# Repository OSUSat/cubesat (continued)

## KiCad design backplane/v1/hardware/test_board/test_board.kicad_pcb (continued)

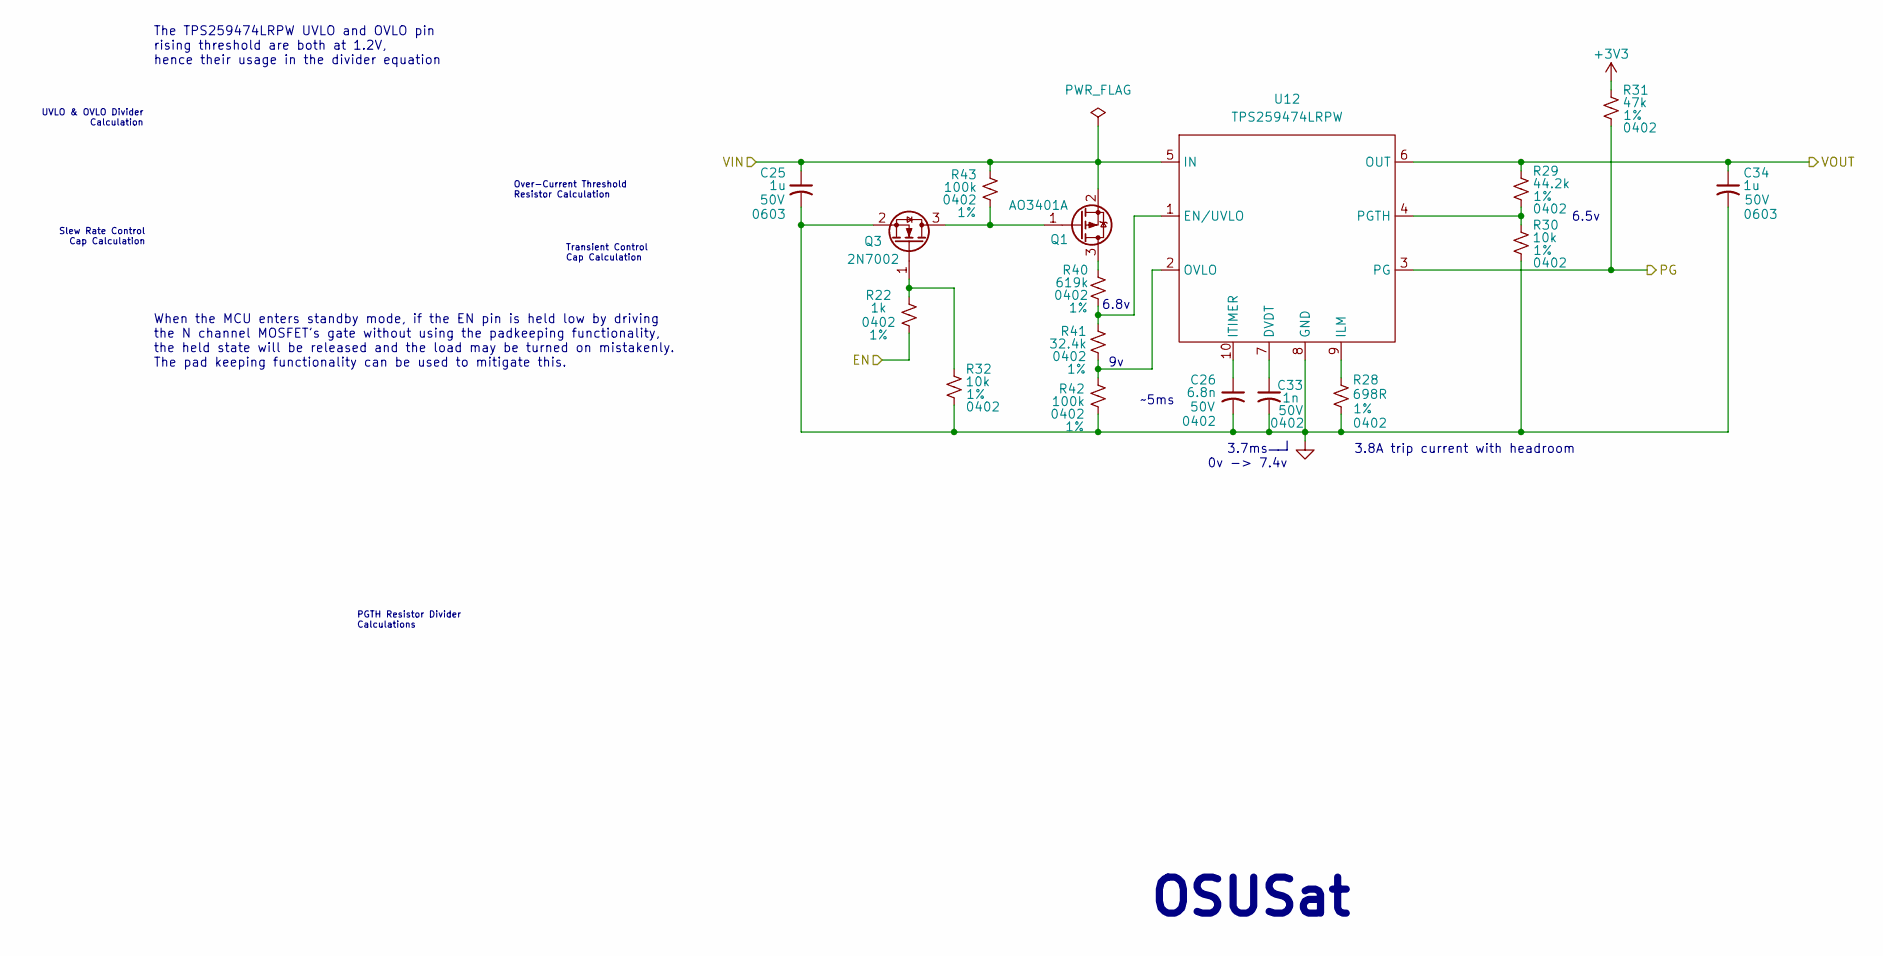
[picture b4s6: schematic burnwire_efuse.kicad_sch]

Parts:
C25, C34: 1u; C_0603_1608Metric; Rating 50V
C26: 6.8n; C_0402_1005Metric; Rating 50V
C33: 1n; C_0402_1005Metric; Rating 50V
Q1: AO3401A; SOT-23
Q3: 2N7002; SOT-23
R22: 1k; R_0402_1005Metric; Tolerance 1%; LCSC PN C21190
R28: 698R; R_0402_1005Metric; Tolerance 1%; LCSC PN C4012675
R29: 44.2k; R_0402_1005Metric; Tolerance 1%; LCSC PN C2933098
R30, R32: 10k; R_0402_1005Metric; Tolerance 1%; LCSC PN C25744
R31: 47k; R_0402_1005Metric; Tolerance 1%; LCSC PN C25792
R40: 619k; R_0402_1005Metric; Tolerance 1%; LCSC PN C247117
R41: 32.4k; R_0402_1005Metric; Tolerance 1%; LCSC PN C2933088
R42, R43: 100k; R_0402_1005Metric; Tolerance 1%; LCSC PN C25741
U12: TPS259474LRPW; TPS2594x; MPN TPS259474LRPW; LCSC C2864845

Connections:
+3V3: R31.1; also elsewhere on the board
/Peripherals/BURNWIRE_EN: R22.1; also elsewhere on the board
/Peripherals/PG: R31.2, U12.3 (PG); also elsewhere on the board
/Peripherals/VOUT: C34.1, R29.1, U12.6 (OUT); also elsewhere on the board
/RAIL_8_VOUT: C25.1, Q1.2 (S), R43.1, U12.5 (IN); also elsewhere on the board
GND: C25.2, C26.2, C33.2, C34.2, Q3.2 (S), R28.2, R30.2, R32.2, R42.2, U12.8 (GND); also elsewhere on the board
unnamed: Q1.3 (D), R40.1
unnamed: Q1.1 (G), Q3.3 (D), R43.2
unnamed: Q3.1 (G), R22.2, R32.1
unnamed: C33.1, U12.7 (DVDT)
unnamed: R40.2, R41.1, U12.1 (EN/UVLO)
unnamed: R28.1, U12.9 (ILM)
unnamed: C26.1, U12.10 (ITIMER)
unnamed: R41.2, R42.1, U12.2 (OVLO)
unnamed: R29.2, R30.1, U12.4 (PGTH)

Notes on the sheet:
~5ms
Over-Current Threshold Resistor Calculation
6.8v
PGTH Resistor Divider Calculations
UVLO & OVLO Divider Calculation
Transient Control Cap Calculation
6.5v
Slew Rate Control Cap Calculation
OSUSat
The TPS259474LRPW UVLO and OVLO pin rising threshold are both at 1.2V, hence their usage in the divider equation
3.8A trip current with headroom
When the MCU enters standby mode, if the EN pin is held low by driving the N channel MOSFET's gate without using the padkeeping functionality, the held state will be released and the load may be turned on mistakenly. The pad keeping functionality can be used to mitigate this.
3.7ms 0v -> 7.4v

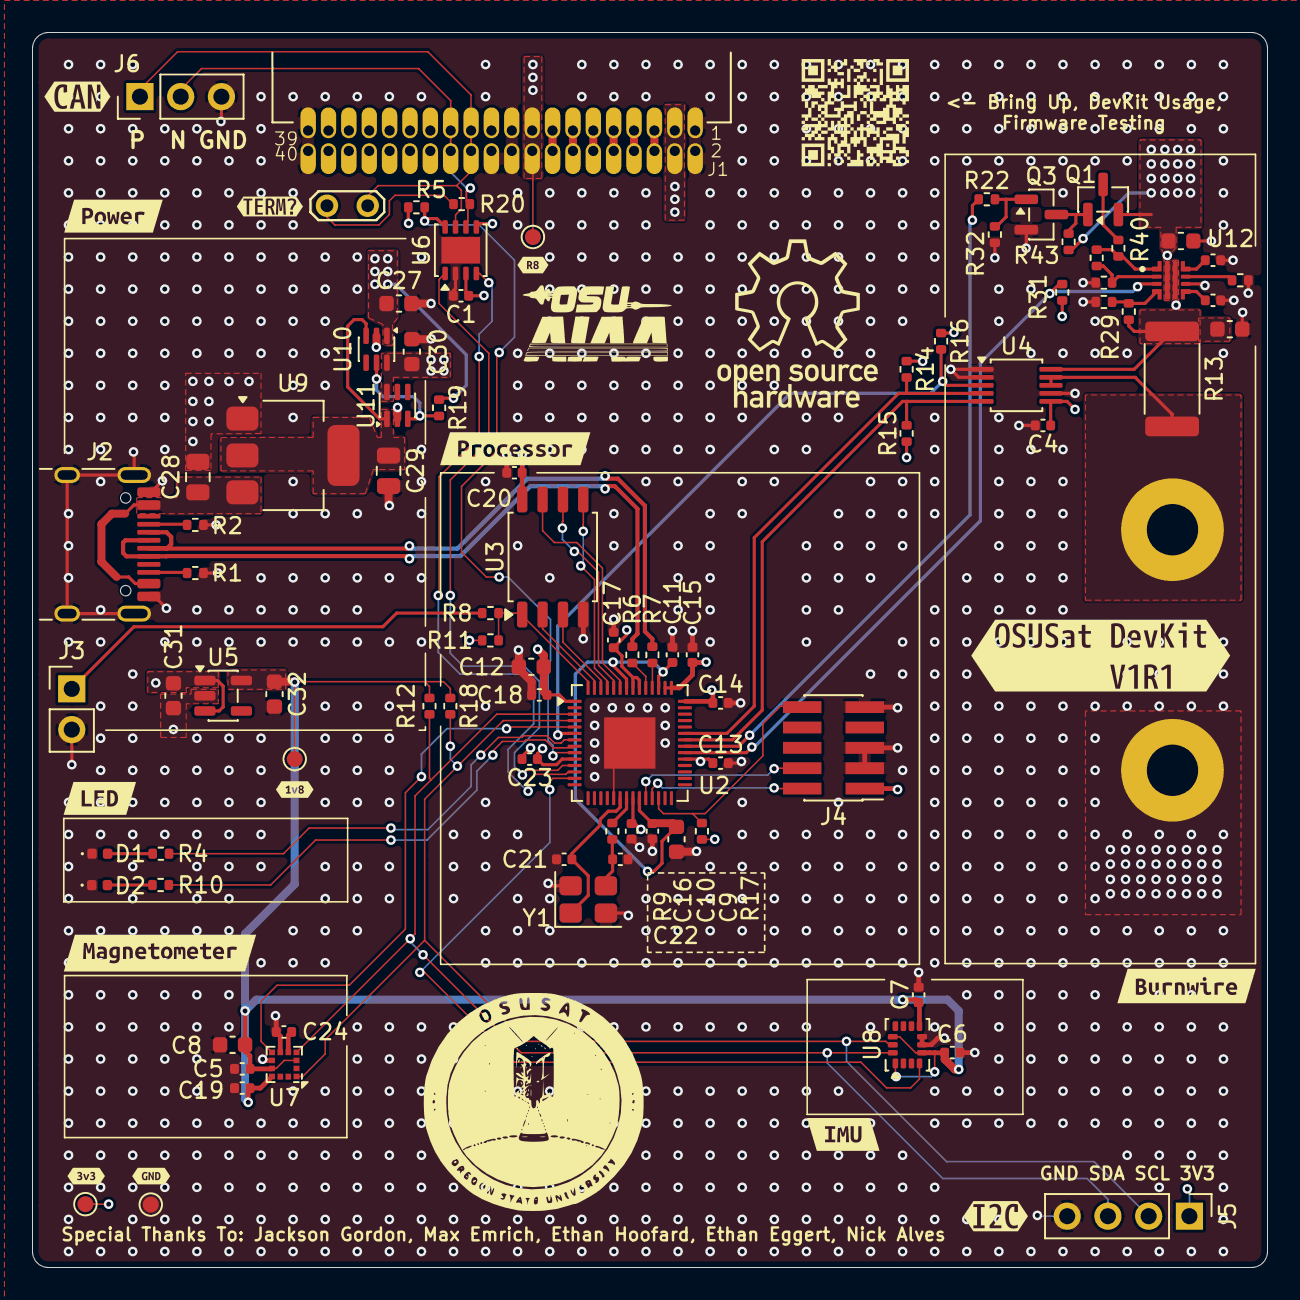
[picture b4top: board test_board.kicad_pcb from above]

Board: 4 copper layers, 77.0 x 77.0 mm, 104 parts (0 on the bottom side), 65 nets.

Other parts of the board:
kibuzzard-6AEEE1A0: G***; kibuzzard-6AEEE1A0
kibuzzard-6AEEE4D9: G***; kibuzzard-6AEEE4D9
kibuzzard-6AEEE4FE: G***; kibuzzard-6AEEE4FE
kibuzzard-6AEEE49C: G***; kibuzzard-6AEEE49C
kibuzzard-6AEEE135: G***; kibuzzard-6AEEE135
kibuzzard-6AEEE141: G***; kibuzzard-6AEEE141
kibuzzard-6AEEE463: G***; kibuzzard-6AEEE463
kibuzzard-6AF0FB3F: G***; kibuzzard-6AF0FB3F
kibuzzard-6AF0FB37: G***; kibuzzard-6AF0FB37
kibuzzard-6AF04FEC: G***; kibuzzard-6AF04FEC
kibuzzard-6AF04FF3: G***; kibuzzard-6AF04FF3
kibuzzard-6AF04FFB: G***; kibuzzard-6AF04FFB
kibuzzard-6AF05A60: G***; kibuzzard-6AF05A60
kibuzzard-6AF14B77: G***; kibuzzard-6AF14B77

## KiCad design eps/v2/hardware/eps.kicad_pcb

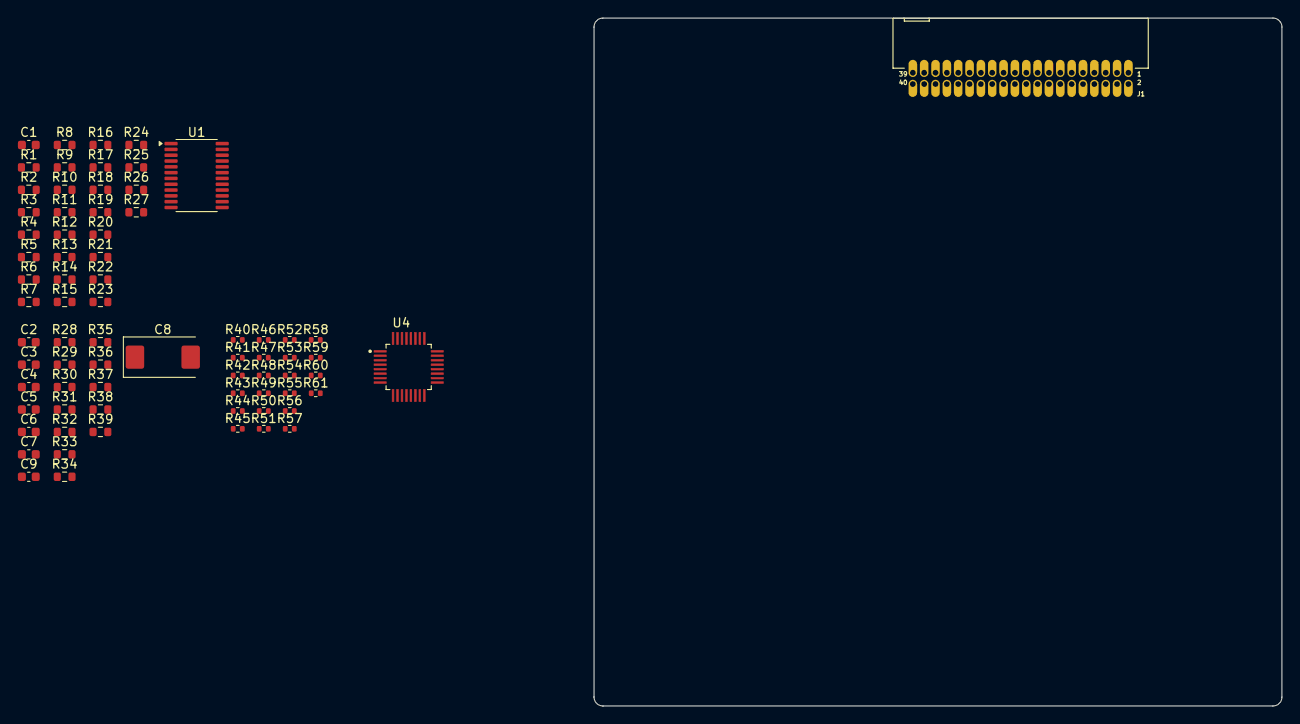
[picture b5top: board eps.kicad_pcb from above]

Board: 2 copper layers, 77.0 x 77.0 mm, 73 parts (0 on the bottom side), 57 nets, no tracks yet.

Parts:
C1: 100n; C_0603_1608Metric
C2, C5: 3.3n 25V; C_0603_1608Metric
C3, C6: 2.2n; C_0603_1608Metric
C4, C7: 1u 25V; C_0603_1608Metric
C8: 220u 25V; CP_EIA-7343-43_Kemet-X
C9: 100n 25V; C_0603_1608Metric
J1: Conn_02x20_Odd_Even; J-SAMTEC-TFM-120-X1-XXX-D-RA
R1, R2, R4, R5, R6, R7, R8, R9, R10, R11, R12, R13, R14, R15, R16, R17, R18, R19: 4.7k; R_0603_1608Metric
R3, R37, R39: 10k; R_0603_1608Metric
R20, R21, R22, R23, R24, R25, R26, R27, R33: 100k; R_0603_1608Metric
R28: 383k; R_0603_1608Metric
R29, R31: 147k; R_0603_1608Metric
R30: 590k; R_0603_1608Metric
R32: 412k; R_0603_1608Metric
R34, R35: 1.13k; R_0603_1608Metric
R36, R38: 220k; R_0603_1608Metric
R40, R41, R42, R43, R44, R45, R46: 47; R_0402_1005Metric
R47, R48, R49, R50, R51, R52, R53, R54, R55, R56, R57, R58: TBD; R_0402_1005Metric
R59, R60, R61: 4.7k; R_0402_1005Metric
U1: TCA9548APWR; TSSOP-24_4.4x7.8mm_P0.65mm
U4: ADS124S08; QFP50P700X700X120-32N

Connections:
+3.3V: U4.15 (IOVDD), U4.16 (DVDD)
+3V3: C1.1, R1.1, R2.1, R3.1, R4.1, R5.1, R6.1, R7.1, R8.1, R9.1, R10.1, R11.1, R12.1, R13.1, R14.1, R15.1, R16.1, R17.1, R18.1, R19.1, R20.1, R36.1, R37.1, R38.1, R39.1, R59.1, R60.1, U1.24 (VCC)
/EPS-ADC-Mux/AIN0: R47.1, R47.2, U4.7 (AIN0)
/EPS-ADC-Mux/AIN1: R48.1, R48.2, U4.6 (AIN1)
/EPS-ADC-Mux/AIN2: R50.1, R50.2, U4.5 (AIN2)
/EPS-ADC-Mux/AIN3: R49.1, R49.2, U4.4 (AIN3)
/EPS-ADC-Mux/AIN4: R51.1, R51.2, U4.3 (AIN4)
/EPS-ADC-Mux/AIN5: R52.1, R52.2, U4.2 (AIN5)
/EPS-ADC-Mux/AIN6: R53.1, R53.2, U4.32 (REFP1/AIN6)
/EPS-ADC-Mux/AIN7: R54.1, R54.2, U4.31 (REFN1/AIN7)
/EPS-ADC-Mux/AIN8: R55.1, R55.2, U4.22 (GPIO0/AIN8)
/EPS-ADC-Mux/AIN9: R56.1, R56.2, U4.21 (GPIO1/AIN9)
/EPS-ADC-Mux/AIN10: R57.1, R57.2, U4.20 (GPIO2/AIN10)
/EPS-ADC-Mux/AIN11: R58.1, R58.2, U4.19 (GPIO3/AIN11)
/EPS-ADC-Mux/CS: R45.2, R60.2, U4.9 (~CS)
/EPS-ADC-Mux/DIN: R44.1, U4.10 (DIN)
/EPS-ADC-Mux/DRDY: R41.1, U4.13 (~DRDY)
/EPS-ADC-Mux/MISO: R42.1, R42.2, U4.12 (DOUT/~DRDY)
/EPS-ADC-Mux/RESET: R40.2, R59.2, U4.18 (~RESET)
/EPS-ADC-Mux/SCLK: R43.1, R43.2, U4.11 (SCLK)
/EPS-ADC-Mux/START/SYNC: R46.1, R46.2, R61.1, U4.8 (START/SYNC)
/Pack-USB-C-Mux/BAT_UVLO: R32.2, R33.1
/Pack-USB-C-Mux/USB_OVLO: R30.2, R31.1
/Pack-USB-C-Mux/USB_UVLO: R28.2, R29.1
CAN_MAIN_N: J1.25, J1.26
CAN_MAIN_P: J1.23, J1.24
EFUSE_I2C_SCL: R1.2, U1.22 (SCL)
EFUSE_I2C_SDA: R2.2, U1.23 (SDA)
EFUSE_R1_SCL: R4.2, U1.5 (SC0)
EFUSE_R1_SDA: R5.2, U1.4 (SD0)
EFUSE_R2_SCL: R6.2, U1.7 (SC1)
EFUSE_R2_SDA: R7.2, U1.6 (SD1)
EFUSE_R3_SCL: R8.2, U1.9 (SC2)
EFUSE_R3_SDA: R9.2, U1.8 (SD2)
EFUSE_R4_SCL: R10.2, U1.11 (SC3)
EFUSE_R4_SDA: R11.2, U1.10 (SD3)
EFUSE_R5_SCL: R12.2, U1.14 (SC4)
EFUSE_R5_SDA: R13.2, U1.13 (SD4)
EFUSE_R6_SCL: R14.2, U1.16 (SC5)
EFUSE_R6_SDA: R15.2, U1.15 (SD5)
EFUSE_R7_SCL: R16.2, U1.18 (SC6)
EFUSE_R7_SDA: R17.2, U1.17 (SD6)
EFUSE_R8_SCL: R18.2, U1.20 (SC7)
EFUSE_R8_SDA: R19.2, U1.19 (SD7)
GND: C1.2, C2.2, C3.2, C4.2, C5.2, C6.2, C7.2, C8.2, C9.2, J1.1, J1.2, J1.19, J1.20, J1.22, J1.39, J1.40, R21.2, R22.2, R23.2, R24.2, R25.2, R26.2, R27.2, R29.2, R31.2, R33.2, R34.2, R35.2, R61.2, U1.1 (A0), U1.2 (A1), U1.12 (GND), U1.21 (A2), U4.1 (AINCOM), U4.14 (DGND), U4.17 (CLK), U4.24 (REFCOM), U4.27 (AVSS), U4.28 (AVSS-SW)
I2C_MUX_RST: R3.2, U1.3 (~RESET)
PACK_V: C7.1, R32.1
RAIL_1_VOUT: J1.3, J1.4
RAIL_2_VOUT: J1.5, J1.6
RAIL_3_VOUT: J1.7, J1.8
RAIL_4_VOUT: J1.9, J1.10
RAIL_5_VOUT: J1.11, J1.12
RAIL_6_VOUT: J1.13, J1.14
RAIL_7_VOUT: J1.15, J1.16
RAIL_8_VOUT: J1.17, J1.18
UNREG: C8.1, C9.1
VUSB_PROT: C4.1, R28.1, R30.1

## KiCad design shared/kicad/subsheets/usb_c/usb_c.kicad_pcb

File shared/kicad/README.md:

# OSUSat Shared KiCad Assets & Templates

This directory contains shared KiCad symbols, footprints, 3D models, design rules, library tables, and project templates for the **OSUSat CubeSat** hardware ecosystem.

---

## Directory Contents

- **`templates/`**: Project templates for standard board configurations (e.g. `test_board` expansion cards).
- **`symbols/`**: Shared subsystem component symbol libraries (`OSUSAT_EPS`, `OSUSAT_OBC`, `OSUSAT_Payload`, etc.).
- **`footprints/`**: Shared PCB footprint libraries (`OSUSAT_Connectors.pretty`, `OSUSAT_ICs.pretty`, etc.).
- **`3dmodels/`**: 3D STEP/WRL CAD models for components and mechanical alignments.
- **`rules/`**: Pre-defined DRC rules and PCB stackup definitions.

---

## Adding Templates to KiCad via Symlinking

Symlinking links the shared repository template directory directly into your local KiCad environment. Any updates pulled from git will be available in KiCad without copying files manually.

### Linux Instructions

1. Open a terminal and ensure your KiCad template directory exists:
   ```bash
   mkdir -p ~/.local/share/kicad/10.0/template
   ```
   *(Replace `10.0` with your installed KiCad version: `10.0`, `9.0`, `8.0`, etc.)*

2. Create a symbolic link pointing to the repository template:
   ```bash
   ln -sf /path/to/cubesat/repo/shared/kicad/templates/test_board ~/.local/share/kicad/10.0/template/test_board
   ```

---

### Windows Instructions

#### Option 1: PowerShell
Run PowerShell and execute:

```powershell
# ensure user template directory exists
New-Item -ItemType Directory -Force -Path "$env:APPDATA\kicad\10.0\template"

# create directory symbolic link
New-Item -ItemType SymbolicLink -Path "$env:APPDATA\kicad\10.0\template\test_board" -Target "C:\path\to\cubesat\repo\shared\kicad\templates\test_board"
```
*(Replace `10.0` and `C:\path\to\cubesat` with your installed KiCad version and repo path).*

#### Option 2: Command Prompt (`cmd.exe`)
Open Command Prompt (Run as Administrator):

```cmd
mkdir "%APPDATA%\kicad\10.0\template"
mklink /D "%APPDATA%\kicad\10.0\template\test_board" "C:\path\to\cubesat\shared\kicad\templates\test_board"
```

---

### Alternative: Configure Path in KiCad GUI

1. Open KiCad.
2. Navigate to **Preferences → Configure Paths...**
3. Under **Environment Variables**, add `KICAD_USER_TEMPLATE_DIR`:
   - **Name**: `KICAD_USER_TEMPLATE_DIR`
   - **Path**: Absolute path to `.../cubesat/shared/kicad/templates`
4. Click **OK**.

---

## Creating a Board from Template

1. Open KiCad.
2. Select **File → New Project from Template...** (or `Ctrl+N`).
3. Click the **User Templates** tab.
4. Select **OSUSat Backplane Test Board Template**.
5. Choose your destination directory and enter your project name (e.g. `payload_card_v1`).
6. Click **Save**.

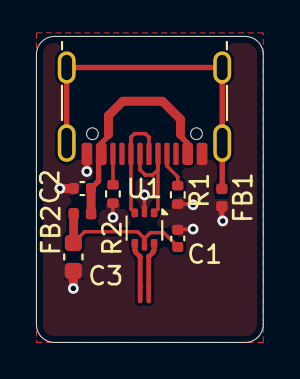
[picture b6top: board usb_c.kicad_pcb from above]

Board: 4 copper layers, 12.6 x 17.0 mm, 9 parts (0 on the bottom side), 8 nets.

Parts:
C1: 100nF; C_0402_1005Metric
C2: 10n; C_0402_1005Metric
C3: 1u; C_0603_1608Metric
FB1, FB2: 120R; L_0402_1005Metric
J1: USB_C_Receptacle_USB2.0_16P; USB_C_Receptacle_G-Switch_GT-USB-7010ASV
R1, R2: 5.1k; R_0402_1005Metric
U1: USBLC6-2P6; SOT-666

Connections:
/USB-C/CC1: J1.A5 (CC1), R1.1
/USB-C/CC2: J1.B5 (CC2), R2.1
/USB-C/FB: FB1.1, J1.SH (SHIELD)
/USB-C/PI: C2.1, FB2.1, J1.A4 (VBUS), J1.A9 (VBUS), J1.B4 (VBUS), J1.B9 (VBUS)
/USB-C/UNPROT_USB_D+: J1.A6 (D+), J1.B6 (D+), U1.3 (I/O2)
/USB-C/UNPROT_USB_D-: J1.A7 (D-), J1.B7 (D-), U1.1 (I/O1)
GND: C1.2, C2.2, C3.2, FB1.2, J1.A1 (GND), J1.A12 (GND), J1.B1 (GND), J1.B12 (GND), R1.2, R2.2, U1.2 (GND)
VBUS: C1.1, C3.1, FB2.2, U1.5 (VBUS)

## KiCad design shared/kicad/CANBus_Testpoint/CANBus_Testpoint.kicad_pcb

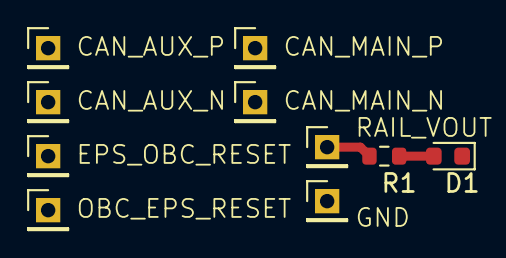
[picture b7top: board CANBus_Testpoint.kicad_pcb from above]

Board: 2 copper layers, 10 parts (0 on the bottom side), 3 nets.

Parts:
CAN_AUX_N_Testpoint1: TP2; PinHeader_1x01_P2.00mm_Vertical
CAN_AUX_P_Testpoint1: TP1; PinHeader_1x01_P2.00mm_Vertical
CAN_MAIN_N_Testpoint1: TP4; PinHeader_1x01_P2.00mm_Vertical
CAN_MAIN_P_Testpoint1: TP3; PinHeader_1x01_P2.00mm_Vertical
D1: LED; LED_0603_1608Metric
EPS_OBC_RESET_Testpoint1: TP5; PinHeader_1x01_P2.00mm_Vertical
GND_Testpoint1: TP8; PinHeader_1x01_P2.00mm_Vertical
OBC_EPS_RESET_Testpoint1: TP6; PinHeader_1x01_P2.00mm_Vertical
R1: R_Small_US; R_0603_1608Metric
RAIL_VOUT_Testpoint1: TP7; PinHeader_1x01_P2.00mm_Vertical

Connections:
/test/RAIL_VOUT: R1.1, RAIL_VOUT_Testpoint1.1 (1_1)
GND: D1.1 (K), GND_Testpoint1.1 (1_1)
unnamed: D1.2 (A), R1.2

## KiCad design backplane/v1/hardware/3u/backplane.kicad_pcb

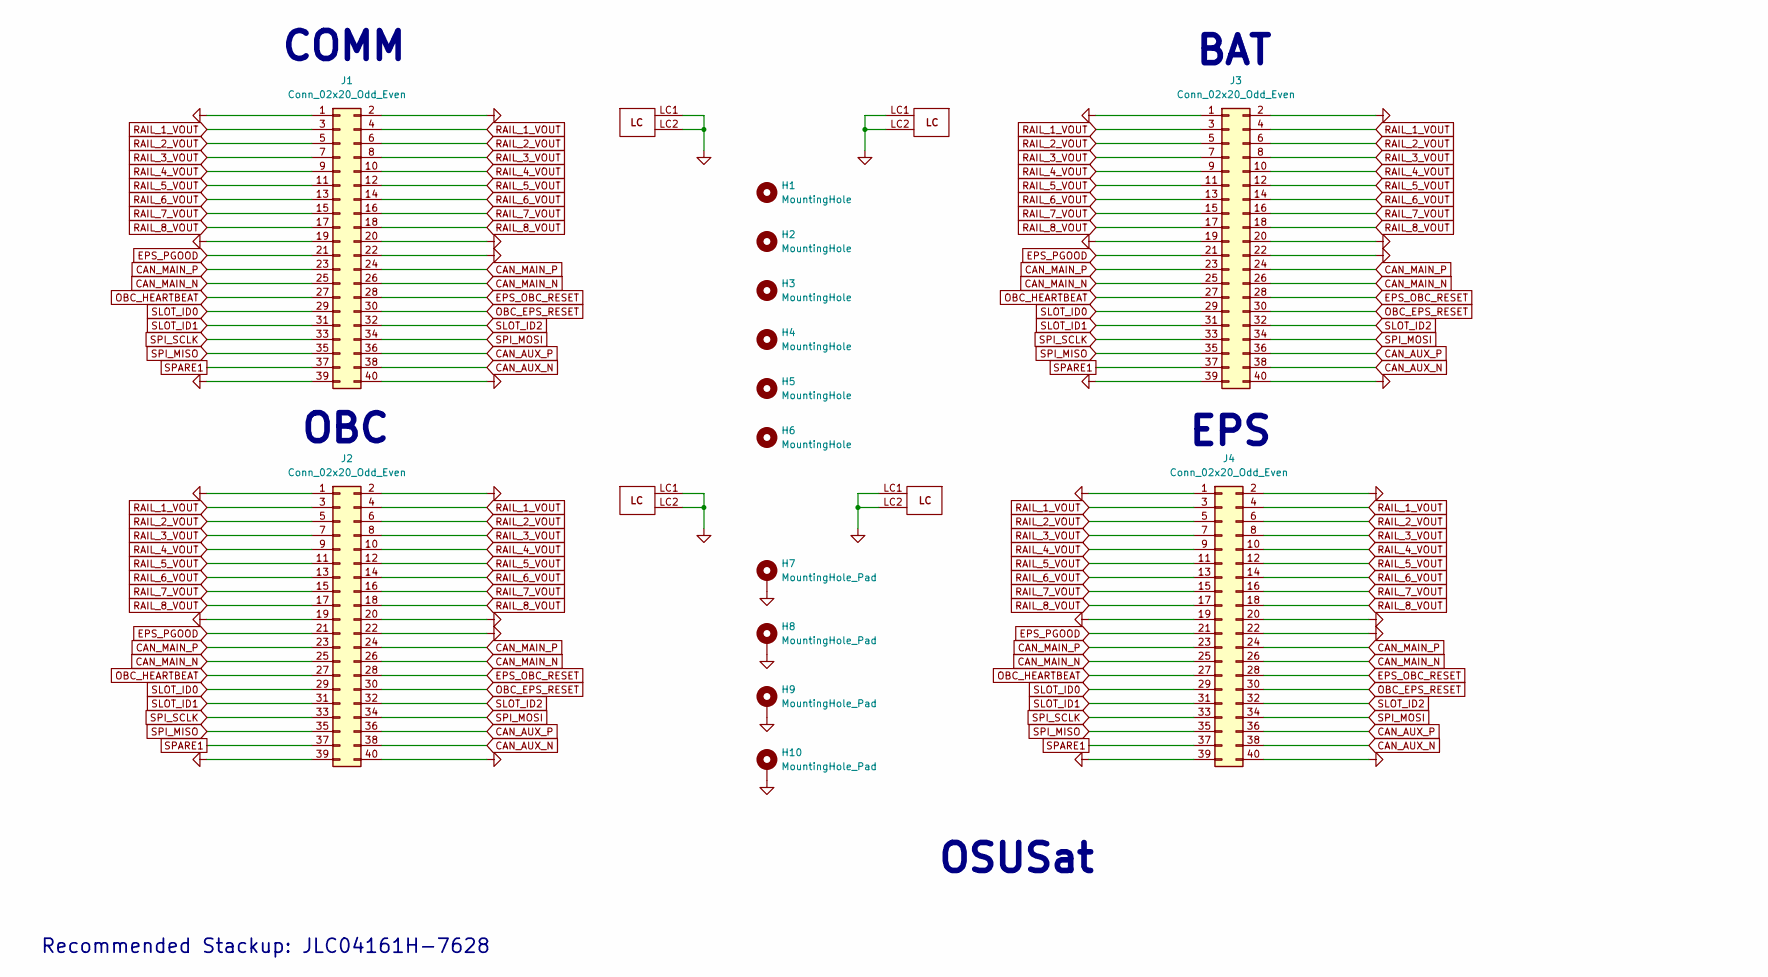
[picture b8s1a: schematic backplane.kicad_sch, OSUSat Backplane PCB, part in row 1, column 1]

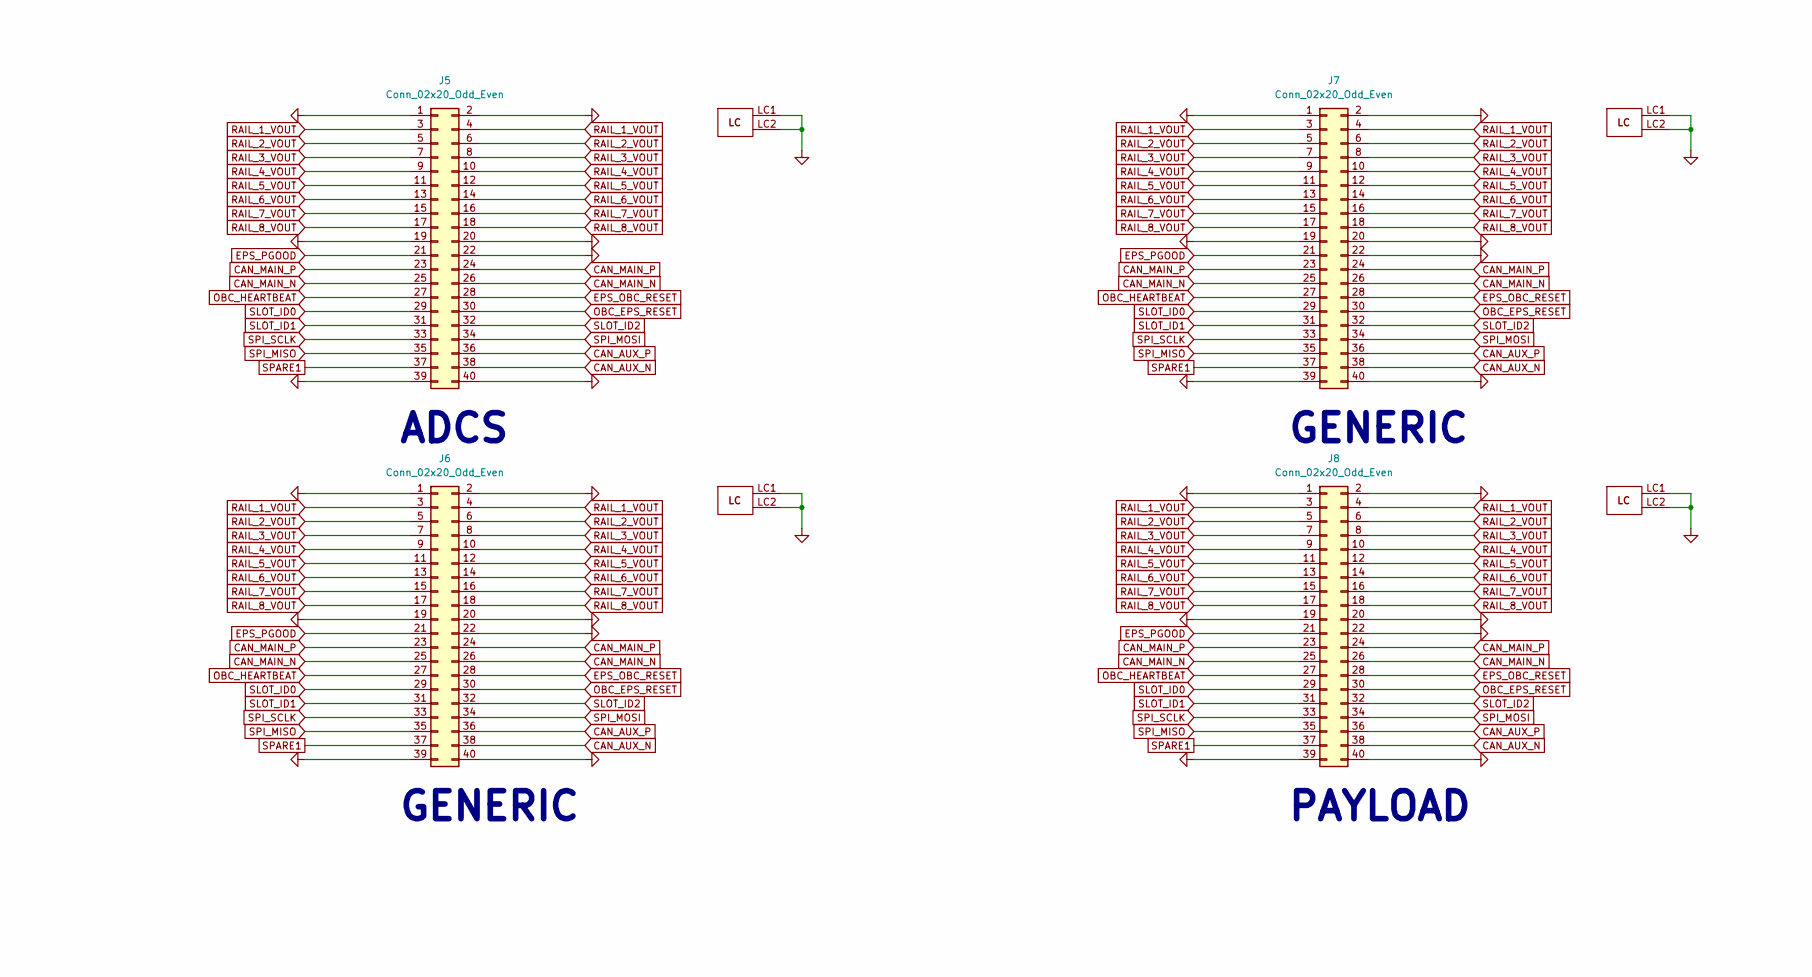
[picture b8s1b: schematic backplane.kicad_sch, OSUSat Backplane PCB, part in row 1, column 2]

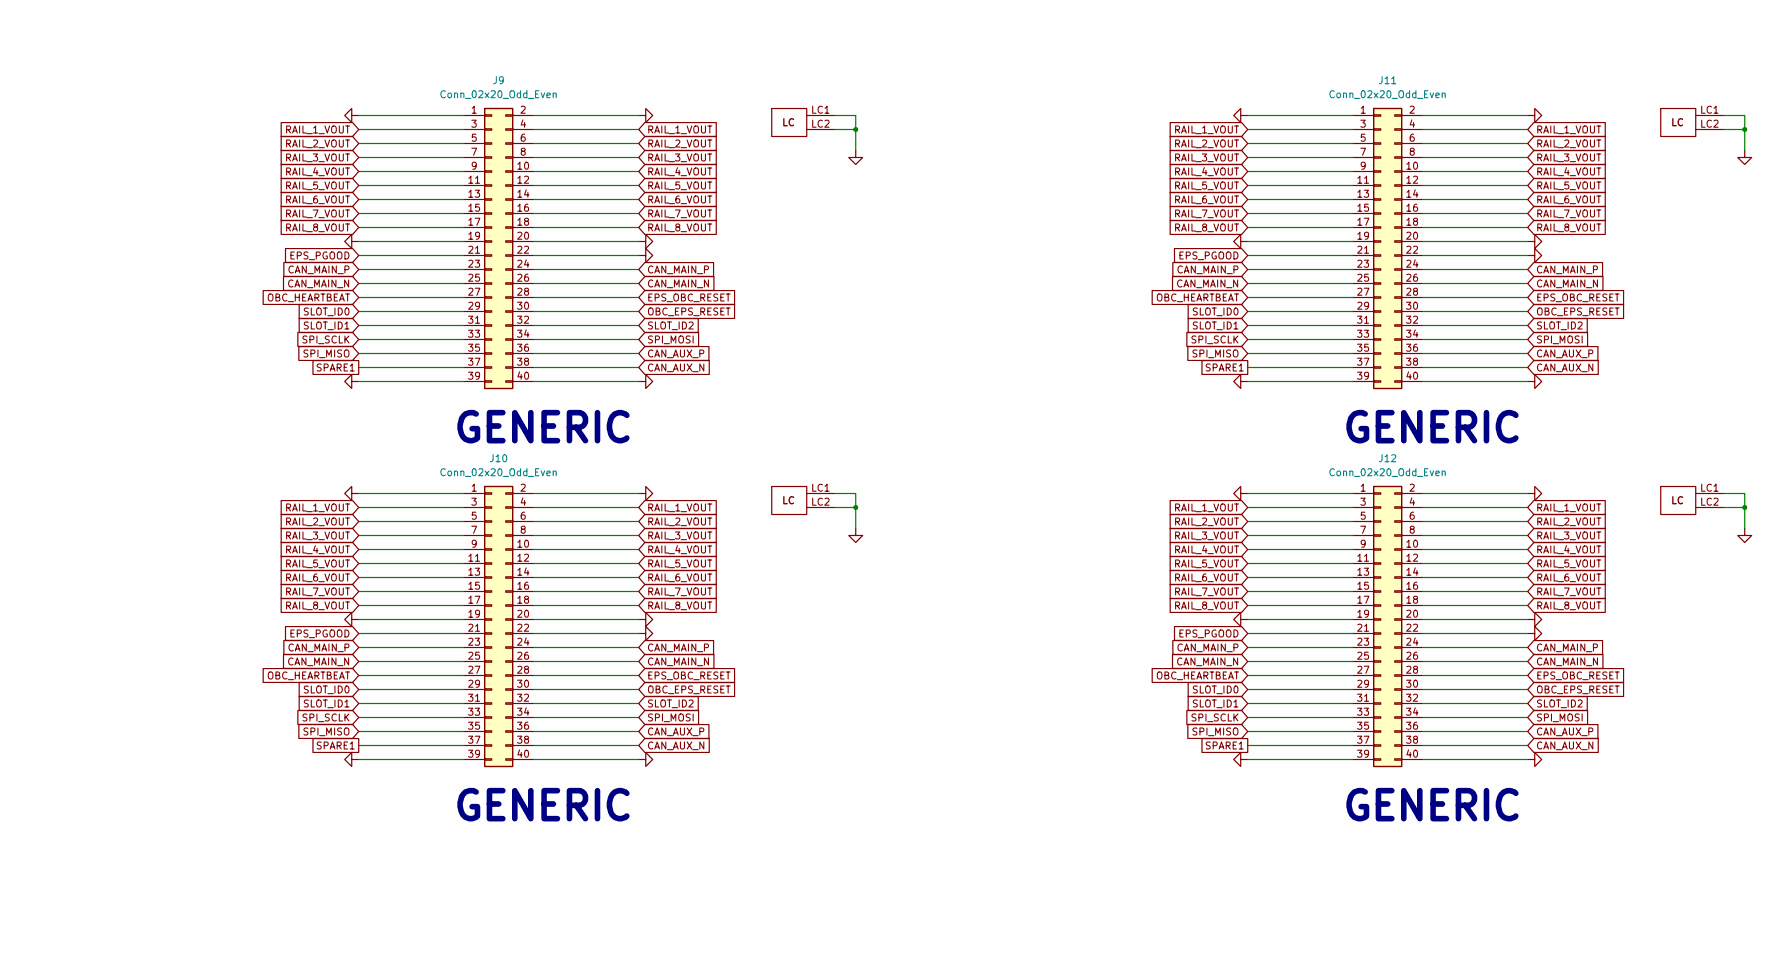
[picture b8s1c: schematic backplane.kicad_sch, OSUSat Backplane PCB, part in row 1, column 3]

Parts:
H1, H2, H3, H4, H5, H6: MountingHole; MountingHole_4.3mm_M4
H7, H8, H9, H10: MountingHole_Pad; MountingHole_3.2mm_M3_Pad
J1, J2, J3, J4, J5, J6, J7, J8, J9, J10, J11, J12: Conn_02x20_Odd_Even; SFM-120-X1-XXX-D

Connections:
CAN_AUX_N: J1.38, J2.38, J3.38, J4.38, J5.38, J6.38, J7.38, J8.38, J9.38, J10.38, J11.38, J12.38
CAN_AUX_P: J1.36, J2.36, J3.36, J4.36, J5.36, J6.36, J7.36, J8.36, J9.36, J10.36, J11.36, J12.36
CAN_MAIN_N: J1.25, J1.26, J2.25, J2.26, J3.25, J3.26, J4.25, J4.26, J5.25, J5.26, J6.25, J6.26, J7.25, J7.26, J8.25, J8.26, J9.25, J9.26, J10.25, J10.26, J11.25, J11.26, J12.25, J12.26
CAN_MAIN_P: J1.23, J1.24, J2.23, J2.24, J3.23, J3.24, J4.23, J4.24, J5.23, J5.24, J6.23, J6.24, J7.23, J7.24, J8.23, J8.24, J9.23, J9.24, J10.23, J10.24, J11.23, J11.24, J12.23, J12.24
EPS_OBC_RESET: J1.28, J2.28, J3.28, J4.28, J5.28, J6.28, J7.28, J8.28, J9.28, J10.28, J11.28, J12.28
EPS_PGOOD: J1.21, J2.21, J3.21, J4.21, J5.21, J6.21, J7.21, J8.21, J9.21, J10.21, J11.21, J12.21
GND: H7.1 (1_1), H8.1 (1_1), H9.1 (1_1), H10.1 (1_1), J1.1, J1.2, J1.19, J1.20, J1.22, J1.39, J1.40, J1.LC1, J1.LC2, J2.1, J2.2, J2.19, J2.20, J2.22, J2.39, J2.40, J2.LC1, J2.LC2, J3.1, J3.2, J3.19, J3.20, J3.22, J3.39, J3.40, J3.LC1, J3.LC2, J4.1, J4.2, J4.19, J4.20, J4.22, J4.39, J4.40, J4.LC1, J4.LC2, J5.1, J5.2, J5.19, J5.20, J5.22, J5.39, J5.40, J5.LC1, J5.LC2, J6.1, J6.2, J6.19, J6.20, J6.22, J6.39, J6.40, J6.LC1, J6.LC2, J7.1, J7.2, J7.19, J7.20, J7.22, J7.39, J7.40, J7.LC1, J7.LC2, J8.1, J8.2, J8.19, J8.20, J8.22, J8.39, J8.40, J8.LC1, J8.LC2, J9.1, J9.2, J9.19, J9.20, J9.22, J9.39, J9.40, J9.LC1, J9.LC2, J10.1, J10.2, J10.19, J10.20, J10.22, J10.39, J10.40, J10.LC1, J10.LC2, J11.1, J11.2, J11.19, J11.20, J11.22, J11.39, J11.40, J11.LC1, J11.LC2, J12.1, J12.2, J12.19, J12.20, J12.22, J12.39, J12.40, J12.LC1, J12.LC2; also elsewhere on the board
OBC_EPS_RESET: J1.30, J2.30, J3.30, J4.30, J5.30, J6.30, J7.30, J8.30, J9.30, J10.30, J11.30, J12.30
OBC_HEARTBEAT: J1.27, J2.27, J3.27, J4.27, J5.27, J6.27, J7.27, J8.27, J9.27, J10.27, J11.27, J12.27
RAIL_1_VOUT: J1.3, J1.4, J2.3, J2.4, J3.3, J3.4, J4.3, J4.4, J5.3, J5.4, J6.3, J6.4, J7.3, J7.4, J8.3, J8.4, J9.3, J9.4, J10.3, J10.4, J11.3, J11.4, J12.3, J12.4
RAIL_2_VOUT: J1.5, J1.6, J2.5, J2.6, J3.5, J3.6, J4.5, J4.6, J5.5, J5.6, J6.5, J6.6, J7.5, J7.6, J8.5, J8.6, J9.5, J9.6, J10.5, J10.6, J11.5, J11.6, J12.5, J12.6
RAIL_3_VOUT: J1.7, J1.8, J2.7, J2.8, J3.7, J3.8, J4.7, J4.8, J5.7, J5.8, J6.7, J6.8, J7.7, J7.8, J8.7, J8.8, J9.7, J9.8, J10.7, J10.8, J11.7, J11.8, J12.7, J12.8
RAIL_4_VOUT: J1.9, J1.10, J2.9, J2.10, J3.9, J3.10, J4.9, J4.10, J5.9, J5.10, J6.9, J6.10, J7.9, J7.10, J8.9, J8.10, J9.9, J9.10, J10.9, J10.10, J11.9, J11.10, J12.9, J12.10
RAIL_5_VOUT: J1.11, J1.12, J2.11, J2.12, J3.11, J3.12, J4.11, J4.12, J5.11, J5.12, J6.11, J6.12, J7.11, J7.12, J8.11, J8.12, J9.11, J9.12, J10.11, J10.12, J11.11, J11.12, J12.11, J12.12
RAIL_6_VOUT: J1.13, J1.14, J2.13, J2.14, J3.13, J3.14, J4.13, J4.14, J5.13, J5.14, J6.13, J6.14, J7.13, J7.14, J8.13, J8.14, J9.13, J9.14, J10.13, J10.14, J11.13, J11.14, J12.13, J12.14
RAIL_7_VOUT: J1.15, J1.16, J2.15, J2.16, J3.15, J3.16, J4.15, J4.16, J5.15, J5.16, J6.15, J6.16, J7.15, J7.16, J8.15, J8.16, J9.15, J9.16, J10.15, J10.16, J11.15, J11.16, J12.15, J12.16
RAIL_8_VOUT: J1.17, J1.18, J2.17, J2.18, J3.17, J3.18, J4.17, J4.18, J5.17, J5.18, J6.17, J6.18, J7.17, J7.18, J8.17, J8.18, J9.17, J9.18, J10.17, J10.18, J11.17, J11.18, J12.17, J12.18
SLOT_ID0: J1.29, J2.29, J3.29, J4.29, J5.29, J6.29, J7.29, J8.29, J9.29, J10.29, J11.29, J12.29
SLOT_ID1: J1.31, J2.31, J3.31, J4.31, J5.31, J6.31, J7.31, J8.31, J9.31, J10.31, J11.31, J12.31
SLOT_ID2: J1.32, J2.32, J3.32, J4.32, J5.32, J6.32, J7.32, J8.32, J9.32, J10.32, J11.32, J12.32
SPARE1: J1.37, J2.37, J3.37, J4.37, J5.37, J6.37, J7.37, J8.37, J9.37, J10.37, J11.37, J12.37
SPI_MISO: J1.35, J2.35, J3.35, J4.35, J5.35, J6.35, J7.35, J8.35, J9.35, J10.35, J11.35, J12.35
SPI_MOSI: J1.34, J2.34, J3.34, J4.34, J5.34, J6.34, J7.34, J8.34, J9.34, J10.34, J11.34, J12.34
SPI_SCLK: J1.33, J2.33, J3.33, J4.33, J5.33, J6.33, J7.33, J8.33, J9.33, J10.33, J11.33, J12.33

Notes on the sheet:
Recommended Stackup: JLC04161H-7628
OSUSat
EPS
COMM
OBC
BAT
ADCS
GENERIC
PAYLOAD

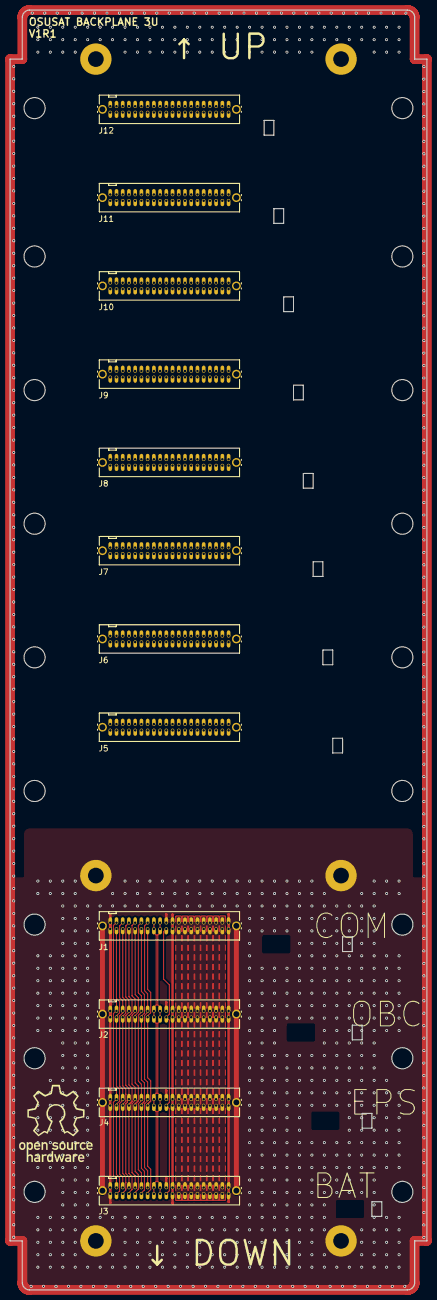
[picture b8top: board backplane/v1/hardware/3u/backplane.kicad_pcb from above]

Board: 4 copper layers, 85.0 x 261.0 mm, 36 parts (0 on the bottom side), 24 nets.

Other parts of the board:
H11, H12, H13, H14, H15, H16, H17, H18, H19, H20, H21, H22: MountingHole; MountingHole_4.3mm_M4
H23, H24: MountingHole_Pad; MountingHole_3.2mm_M3_Pad

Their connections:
GND: H23.1 (1_1), H24.1 (1_1); also elsewhere on the board

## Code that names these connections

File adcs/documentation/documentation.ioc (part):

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Mcu.Name=STM32L4Q5CGTxP
Mcu.Package=LQFP48
Mcu.UserName=STM32L4Q5CGTxP
PA0.Signal=S_TIM2_CH1
PA1.Signal=S_TIM2_CH2
PA10.Signal=USART1_RX
PA11.Signal=USB_OTG_FS_DM
PA12.Signal=USB_OTG_FS_DP
PA13\ (JTMS/SWDIO).Signal=SYS_JTMS-SWDIO
PA14\ (JTCK/SWCLK).Signal=SYS_JTCK-SWCLK
PA2.Signal=S_TIM2_CH3
PA3.Signal=GPIO_Input
PA4.Signal=GPIO_Output
PA5.Signal=GPIO_Output
PA6.Signal=GPIO_Output
PA7.Signal=GPIO_Output
PA9.Signal=USART1_TX
PB0.Signal=TIM1_CH2N
PB10.Signal=GPIO_Output
PB12.Signal=GPIO_Output
PB13.Signal=I2C2_SCL
PB14.Signal=I2C2_SDA
PB2.Signal=GPIO_Output
PB3\ (JTDO/TRACESWO).Signal=SYS_JTDO-SWO
PB4\ (NJTRST).Signal=I2C3_SDA
PB5.Signal=GPIO_Output
PB6.Signal=I2C1_SCL
PB7.Signal=I2C1_SDA
PB9.Signal=GPIO_Output
RCC.HSE_VALUE=8000000
board=custom

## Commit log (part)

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2026-03-16 fix all obvious schematic issues
2026-03-16 optimize battery charger layout
2026-03-16 change footprint sizes for current monitoring
2026-03-22 start placement of one current monitor
2026-03-23 add better current monitoring layout
2026-03-25 multichannel routing
2026-03-30 fix placements and start routing voltage regulator
2026-04-01 add power decoupling and start placing solar protection
2026-04-02 update footprints for solar protection
2026-04-08 more layout
2026-04-13 finish all current monitor placements
2026-04-15 finish battery charger passive placement
2026-04-15 ensure main-loop is time bounded & make UART Tx non-blocking
2026-04-15 conditionally switch between time-bounded main loop for host builds
2026-04-15 deploy: 682bf4701f957a3fe76d01765209b6a11fcbb0c3
2026-04-15 deploy: 117b69a5a9404e814f1447b90db3134d894f16a9
2026-04-16 finish rc filter passive placement & start other passives
2026-04-20 continue component placement
2026-04-20 deploy: 4c601017c348146119dd5a8288a31c537a8ac5e4
2026-04-20 finish placement for LTC4115 #2
2026-04-20 deploy: 710283f639a0fc93d39ea0d44a9b0fa3e2b65bf9
2026-04-28 add mounting holes and fiducials
2026-04-28 deploy: 632f676ebb73fb96af093ff68a355ae86f40037f
2026-05-01 finish component placement
2026-05-01 deploy: 816692bd0e5431f5031e21557eaddfe2b8ffeff2
2026-05-01 deploy: 055ad93942eebb55ed2e30aa856a6cd84980aead
2026-05-04 continue routing battery charger
2026-05-04 finish routing battery chargers
2026-05-05 fix battery charger issues and finish regulators
2026-05-07 finish routing MPPT controller
2026-05-08 route MCU power
2026-05-08 start routing power path
2026-05-13 continue routing
2026-05-16 bootstrap payload board
2026-05-16 deploy: 75d03f6ecc986cac30348b27a17526e68b3384a3
2026-05-16 route partial power path
2026-05-18 almost finish routing power path
2026-05-19 route 4/6 current monitors
2026-05-19 fix issues with current monitor routing
2026-05-19 route 6/8 current monitors
2026-05-21 route all current monitors
2026-05-23 update license
2026-05-23 deploy: b4c99d20f76f4e24a9c4b5757271e6bfbcfdc346
2026-05-23 deploy: a18c728a11d59b6ff94b4438eba3b5dbccb4e835
2026-05-23 route all current monitor load switch signals
2026-05-23 deploy: 2233d176565cb1a612419bab4996087a216d6829
2026-05-23 start routing i2c signals
2026-05-23 deploy: facafa93a4de93c977d56824fc5723ed9a56a5a0
2026-05-24 clean up schematic, adjust power, add oscillators
2026-05-24 added SD card
2026-05-25 add RTC battery and sensors, preliminary layout
2026-05-25 added CAN, UART, supervisor, USB, power OR-ing, GPS, did layout
2026-05-25 Redid silkscreen
2026-05-25 add BOM and fix tons of hardware bugs
2026-05-25 deploy: 6f0a242c8aa44f1e21d35e99f645f1473808efc2
2026-05-25 MIPI connector added
2026-05-25 added the motordriver to payload schematic
2026-05-26 add SCRT and OSU AIAA logos, add IMU, add PPS LED, hook up some IOs
2026-05-26 schematic cleanup, move to schottky diode for VBAT
2026-05-26 added pins
2026-05-27 finish most routing
2026-05-27 get rid of datasheets
2026-05-27 deploy: dd94f1cb2830cf040fefb21da04b517d941d7d08
2026-05-27 add antenna supervisor, ESD, reroute some stuff
2026-05-27 fix some more bugs
2026-05-27 cleanup
2026-05-27 deploy: 2947518203a8346dfdb0d3150dbfa5fa6898812a
2026-05-27 routed the remaining tracks, adjusted some pours
2026-05-27 silkscreen and DRC fixes
2026-05-27 final tweaks from me
2026-05-27 deploy: f036259e13c3f59cc540ad9838199d6707457d52
2026-05-27 deploy: 85c949962eb9b85d4e96faca26b8841e7f029773
2026-05-27 finish
2026-05-27 deploy: 3dde3707016d7a9f714c0fca21c8cbfae43096a0
2026-05-27 add TVS diodes, rotate decoupling capacitors
2026-05-28 ground via spam
2026-05-28 added github QR code, fixed DRC violations, cleaned up silk
2026-05-30 add limited power supply capabilities as a backup
2026-05-30 interboard connector and organization
2026-05-31 add user LEDs, fix silkscreen
2026-05-31 fix mounting hole positions
2026-05-31 re-lock mounting holes & edge cuts
2026-05-31 rotate bottom inter-board connector to avoid overlapping alignment pins
2026-05-31 swap some pins for better routing, add UART, add more part numbers
2026-05-31 LED part numbers
2026-05-31 DNP parts that JLC shouldn't assemble
2026-05-31 hook up UART to a second set of pins in case it's backwards
2026-05-31 more UART, remove vias that interfere with important parts of the QR code
2026-05-31 deploy: d22244ef4ae43760449501dd8ca0430bd6a6382a
2026-05-31 add names
2026-05-31 move silk away from QR code
2026-05-31 deploy: 2e0c36f5192854d42e49c3bda386c847304fda57
2026-05-31 deploy: 9e49c7343ac63e72928ea98104aa35bf6cf0b203
2026-05-31 forgot to save
2026-05-31 deploy: 84640b485fa42f60cb66598abe6f8d8627eb7a3d
2026-06-01 create CM4 symbol
2026-06-01 remove .history
2026-06-01 add camera symbol, hook up to CM4, add CM4 footprint
2026-06-01 do some layout, route camera differential pairs, add inter-board connector, pick parts for CAN
2026-06-01 did it not save again?
2026-06-01 add STM32CubeMX bootstrapping project
2026-06-01 deploy: b6e8714841111cb64aa0871003bc1f498103c66a
2026-06-01 deploy: 4d62bd94c807bb5db1fd2ab43d416f98f880ca5d
2026-06-01 update BSP and eps config header with new stm32cubemx pinouts
2026-06-01 clean up comments in eps_config.h
2026-06-01 deploy: e7c89c476112cd3e56bc6ab7394f30833e04ab7f
2026-06-01 deploy: 77df87bb8d1ec99b7d2968328ed7b11490d097e3
2026-06-01 implement watchdog service and unit tests
2026-06-01 Implement Telemetry Service and add unit tests
2026-06-01 deploy: 34cbe904a1a92b72395915ef63b8524d83870839
2026-06-01 fix swapped assignments and implement load switching in rail controller
2026-06-01 add non-blocking command handler and redundancy failover
2026-06-01 implement real battery sensor readings and charge control
2026-06-01 implement mppt hardware interface and unit tests
2026-06-01 restore redundancy manager event subscriptions and fault mapping
2026-06-01 integrate power policies with redundancy health status and add mppt cooldown scheduling
2026-06-01 add part of a motor driver
2026-06-01 add second camera connector, but all the pairs are backwards
2026-06-01 fix watchdog unit test link errors and assert gpio states
2026-06-01 address watchdog safety comments and add test case
2026-06-01 update WDI pin on MCU in firmware config
2026-06-01 deploy: f2cacf221dde2b0da984775d450f921e9cf296b4
2026-06-01 deploy: 4b0815c46ceb3321baa0ea7553ea227675828310
2026-06-01 deploy: 67439916409ad3b5cd92b012f3414af9007ec1c6
2026-06-01 integrate watchdog into event bus
2026-06-01 deploy: 364cc2c02e268efe32ab43757507601ff196a403
2026-06-01 add volatile keyword to multi-context busy field in i2c driver
2026-06-01 implement I2C software timeout and unit tests
2026-06-01 deploy: 70232ed2387f3a8942c8f63588f0f9b411fa8af2
2026-06-01 edit comments
2026-06-01 deploy: e3aeaecd34f6330c8076a4c8c1fa34fcc1275ed9
2026-06-01 deploy: ea01802c128408809975d7767f99c4b5119fd221
2026-06-02 clean
2026-06-02 integrate telemetry service with event bus
2026-06-02 initialize telemetry with service references
2026-06-02 fix redundancy degraded components initialization in telemetry test
2026-06-02 integrate battery service and publish EVENT_SYSTICK in main loop
2026-06-02 deploy: 43b4d38c2a450c7a04c1b85bb9eb90585ac99424
2026-06-02 deploy: 9dab2816c24eeeb3b05b0245377fc40f3b91e3e1
2026-06-02 deploy: 38e3504e01e5a06b614aab04eb6c9daa003bbf1d
2026-06-02 implement CANbus HAL driver and SN65HVD230 transceiver support
2026-06-02 update gitignore
2026-06-02 add ethernet
2026-06-05 modifications
2026-06-06 finish CANbus schematic and fix USB
2026-06-06 motor driver schematic, work on high speed routing
2026-06-06 routing, via spam around camera 1, length match pairs for camera 1
2026-06-06 length match but better
2026-06-06 length match but even better
2026-06-06 via spam, silk
2026-06-06 add decoupling caps, fix USB skew, add Jax's name
2026-06-06 ERC fixes, nits, NC
2026-06-06 DRC fixes and add 3d models
2026-06-06 add battery contact PCB
2026-06-07 added through holes
2026-06-07 mounting holes
2026-06-08 add digikey part numbers
2026-06-08 add battery contact PCBs
2026-06-10 deploy: a32c4c6acbee82c78b0298e06f5669376223e8ca
2026-06-10 deploy: 89768ab4f14dbcc272dcb4451e9a405559a2bfef
2026-06-10 add extra grounding vias, open source hardware silk, and make release
2026-06-10 deploy: 762c236243359bd7f7a565d13b9c8b51481ee198
2026-06-10 add production manifests
2026-06-15 add hardware bugs
2026-06-15 update BOM and crystal pinout to passive crystal
2026-06-17 update bsp & start fixes for wdt
2026-06-17 deploy: e38c8fe3819184bf9501b111a8ffe7c50885ed22
2026-06-17 deploy: f2a493d6d3148a08f791b65424afcdd948c6c334
2026-06-17 add CANBus logging
2026-06-17 add log to flash & over CANBus
2026-06-17 update comparator circuit and load switch details
2026-06-18 add ideal diode bug
2026-06-18 update ideal diode specifications in documentation
2026-06-18 telemetry & adc & rail management
2026-06-18 fix(eps): guard debug MCU HAL calls for host builds
2026-06-18 fix issues with CI/CD failing on HITL
2026-06-18 deploy: 0b62aa01cf1aabbb9251d618b6cf9438fff19e57
2026-06-18 deploy: 30a057360201505bf0371af695d686c48dc2bf22
2026-06-18 skeleton OBC firmware
2026-06-18 fix bootstrapping and independent power supply
2026-06-18 downclock obc
